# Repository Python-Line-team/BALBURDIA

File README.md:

# BALBURDIA
Projeto completo de um robô desenhado para a OBR

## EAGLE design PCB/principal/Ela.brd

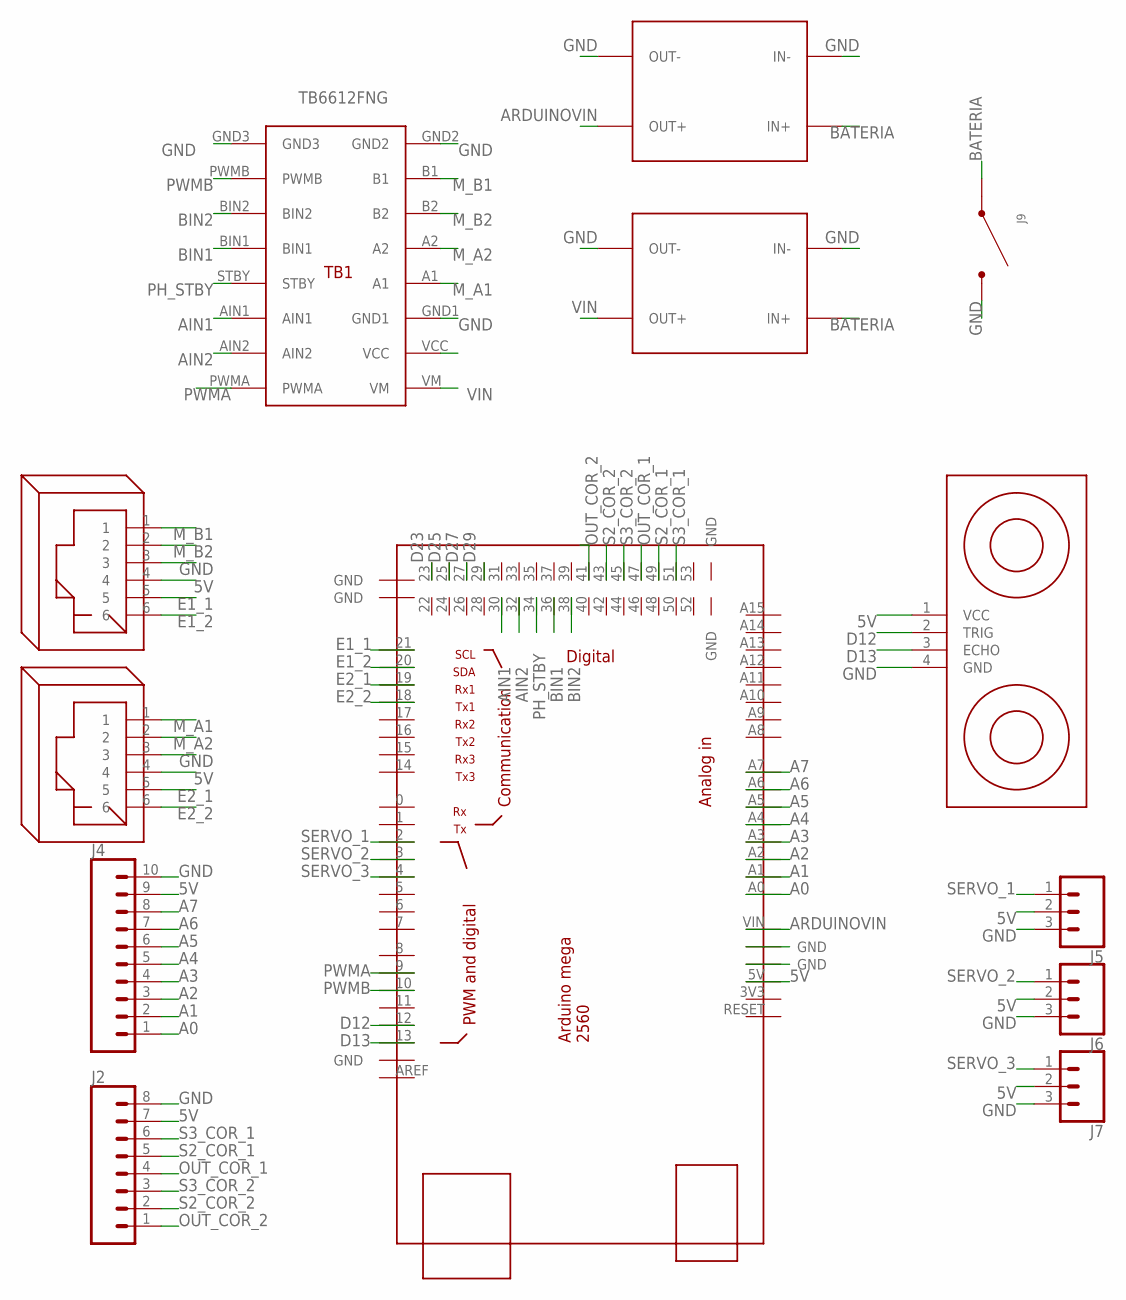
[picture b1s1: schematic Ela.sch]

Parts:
J1, J3: RJ12
J2: CONN_08LONGPADS; 1X08_LONGPADS
J4: CONN_10"; 1X10
J5, J6, J7: CONN_03LONGPADS; 1X03_LONGPADS
J9: XT60TOP; XT60_TOP
TB1: TB6612FNG
U$1: ULTRASONIC-HC-SR04#V
U$2, U$4: DC-DC-STEP-DOWN-LM2596
U$3: MEGA_DEVICE; MEGAOUTLINE

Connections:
5V: J1.4, J2.7, J3.4, J4.9, J5.2, J6.2, J7.2, TB1.VCC, U$1.1 (VCC), U$3.5V
A0: J4.1, U$3.A0
A1: J4.2, U$3.A1
A2: J4.3, U$3.A2
A3: J4.4, U$3.A3
A4: J4.5, U$3.A4
A5: J4.6, U$3.A5
A6: J4.7, U$3.A6
A7: J4.8, U$3.A7
AIN1: TB1.AIN1, U$3.30
AIN2: TB1.AIN2, U$3.32
ARDUINOVIN: U$3.VIN, U$4.OUT+
BATERIA: J9.P$+ (+), U$2.IN+, U$4.IN+
BIN1: TB1.BIN1, U$3.36
BIN2: TB1.BIN2, U$3.38
D12: U$1.2 (TRIG), U$3.12
D13: U$1.3 (ECHO), U$3.13
D23: U$3.23
D25: U$3.25
D27: U$3.27
D29: U$3.29
E1_1: J1.5, U$3.21
E1_2: J1.6, U$3.20
E2_1: J3.5, U$3.19
E2_2: J3.6, U$3.18
GND: J1.3, J2.8, J3.3, J4.10, J5.3, J6.3, J7.3, J9.P$- (-), TB1.GND1, TB1.GND2, TB1.GND3, U$1.4 (GND), U$2.IN-, U$2.OUT-, U$4.IN-, U$4.OUT-
M_A1: J3.1, TB1.A1
M_A2: J3.2, TB1.A2
M_B1: J1.1, TB1.B1
M_B2: J1.2, TB1.B2
OUT_COR_1: J2.4, U$3.47
OUT_COR_2: J2.1, U$3.41
PH_STBY: TB1.STBY, U$3.34
PWMA: TB1.PWMA, U$3.9
PWMB: TB1.PWMB, U$3.10
S2_COR_1: J2.5, U$3.49
S2_COR_2: J2.2, U$3.43
S3_COR_1: J2.6, U$3.51
S3_COR_2: J2.3, U$3.45
SERVO_1: J5.1, U$3.2
SERVO_2: J6.1, U$3.3
SERVO_3: J7.1, U$3.4
VIN: TB1.VM, U$2.OUT+

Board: 2 copper layers, 13 parts (2 on the bottom side), 39 nets, no tracks yet.

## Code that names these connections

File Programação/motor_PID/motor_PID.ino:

#include <SparkFun_TB6612.h>

#define AIN1 36 // 32 //
#define BIN1 32 // 36 //
#define AIN2 30 // 38 //
#define BIN2 38 // 30 //
#define PWMA 9 // 10 //
#define PWMB 10 // 9 //
#define STBY 34

const int offsetA = 1;
const int offsetB = 1;

byte velocidade = 200;

Motor motor1 = Motor(AIN1, AIN2, PWMA, offsetA, STBY);
Motor motor2 = Motor(BIN1, BIN2, PWMB, offsetB, STBY);
//==============================================
#include <QTRSensors.h>

QTRSensors qtr;

const uint8_t SensorCount = 8;
uint16_t sensorValues[SensorCount];

//float  KP = 20, KI = 0.5, KD = 15;
float  KP = 7, KI = 0.5, KD = 6;
int ERRO, erroAnterior = 0, setPoint = 3500;
int velocidadeMotor1 = velocidade;
int velocidadeMotor2 = velocidade;
//==============================================
byte seguirLinha = 1;
void setup(){
  // configure the sensors
  qtr.setTypeAnalog();
  qtr.setSensorPins((const uint8_t[]){A7, A6, A5, A4, A3, A2, A1, A0}, SensorCount);

  delay(500);

  for (uint16_t i = 0; i < 200; i++){
    
      if (i < 25 || (i > 50 && i < 75)|| (i > 100 && i < 125)|| (i > 150 && i < 175)){
        forward(motor1, motor2, 150);
      }else{
        back(motor1, motor2, -150);
      }
    qtr.calibrate();
  }
  brake(motor1, motor2);
  Serial.begin(9600);
  delay(5000);  
}

void loop(){
  while(seguirLinha == 1){
    int ERRO = qtr.readLineBlack(sensorValues) - setPoint;
    ERRO = map(ERRO, -3500, 3500, -velocidade, velocidade);
    int sinalControlador = KP * ERRO + KI* ERRO + KD * (ERRO - erroAnterior);
    erroAnterior = ERRO;
  
    int novaVelocidadeMotor1 = velocidadeMotor1 - sinalControlador;
    int novaVelocidadeMotor2 = velocidadeMotor2 + sinalControlador;
  
    if (novaVelocidadeMotor1 < 0)
      novaVelocidadeMotor1 = 0;
    if (novaVelocidadeMotor2 < 0)
      novaVelocidadeMotor2 = 0;
   
    if (novaVelocidadeMotor1 > 255)
      novaVelocidadeMotor1 = 255;
    if (novaVelocidadeMotor2 > 255)
      novaVelocidadeMotor2 = 255;
  
    motor1.drive(novaVelocidadeMotor1);
    motor2.drive(novaVelocidadeMotor2);
 
    qtr.readCalibrated(sensorValues);
  
    for(int aux = 0;aux <= 5; aux++){
       if (sensorValues[aux]> 800 && sensorValues[aux+1]> 800 &&
       sensorValues[aux+2]> 800 && sensorValues[aux+3]> 800){
          brake(motor1, motor2);
          seguirLinha = 0;
       }
    }
  }
}

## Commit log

2020-11-13 adicionei os principais arquivos que tenho de maneira organizada
2020-11-18 :books: Classe de sensor de cor corrigida

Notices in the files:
parts and their libraries:
SparkFun-Connectors: Licensing: Creative Commons ShareAlike 4.0 International - https://creativecommons.org/licenses/by-sa/4.0
diy-modules: Released under the Creative Commons Attribution 4.0 International License: http://creativecommons.org/licenses/by/4.0
